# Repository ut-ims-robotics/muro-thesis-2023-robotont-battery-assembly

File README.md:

# muro-thesis-2023-robotont-battery-assembly

## ENG
Welcome to the repository for Robotont's battery assembly mechanics and 12 V voltage regulator. This repository includes KiCad project files, pictures, renders and videos that illustrate development of Robotont.

Production files for battery locking mechanism are part of gen3 Robotont development and can be found at this [repository](https://github.com/robotont/robotont-mechanics).

KiCad project files and production files for battery data adapter can be found at this [repository](https://github.com/robotont/robotont-electronics-battery-adapter).

KiCad project files and production files for voltage regulator can be found at this [folder](https://github.com/ut-ims-robotics/muro-thesis-2023-robotont-battery-assembly/tree/main/12V_DC_DC_converter). The whole design of unified PCB which integrates the voltage regulator can be found at this [repository](https://github.com/robotont/robotont-electronics-mainboard).

## EST 
Tere tulemast Robotondi akumehhanismi ja 12 V pingeregulaatori hoidlasse. Selles hoidlas on KiCadi projektifailid ning leidub samuti pilte, videosid ja 3D visualiseeringuid , mis illustreerivad Robotondi arendusprotsessi.

Aku lukustusmehanismi tootmisfailid on osa gen3 Robotondi arendusest ja asuvad siin [hoidlas](https://github.com/robotont/robotont-mechanics).

KiCadi projekti- ja tootmisfailid aku andmevahetuse adapteri jaoks asuvad siin [hoidlas](https://github.com/robotont/robotont-electronics-battery-adapter).

KiCadi projekti- ja tootmisfailid pingeregulaatori jaoks asuvad siin [kaustas](https://github.com/ut-ims-robotics/muro-thesis-2023-robotont-battery-assembly/tree/main/12V_DC_DC_converter). Kogu ühtse trükkplaadi disain (kuhu on integreeritud ka käesolev pingeregulaator) koos tootmisfailidega asub siin [hoidlas](https://github.com/robotont/robotont-electronics-mainboard).

## Battery Locking Mechanism / Aku Lukustusmehhanism
3D model and prototype of battery locking mechanism for Robotont:

Locking mechanism and battery in 2nd gen robot assembly:

## Battery Data Adapter / Aku Andmevahetuse Adapter
The following figures visualize the front side of the PCB along with the 3D model of the design:

## Voltage Regulator / Pingeregulaator

The following figures visualize the front side of the PCB along with the KiCad model of the design:

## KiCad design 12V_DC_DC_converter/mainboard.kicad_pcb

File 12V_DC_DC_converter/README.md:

# 12 V dc dc converter
Voltage regulator for the 3rd generation robotont robot.

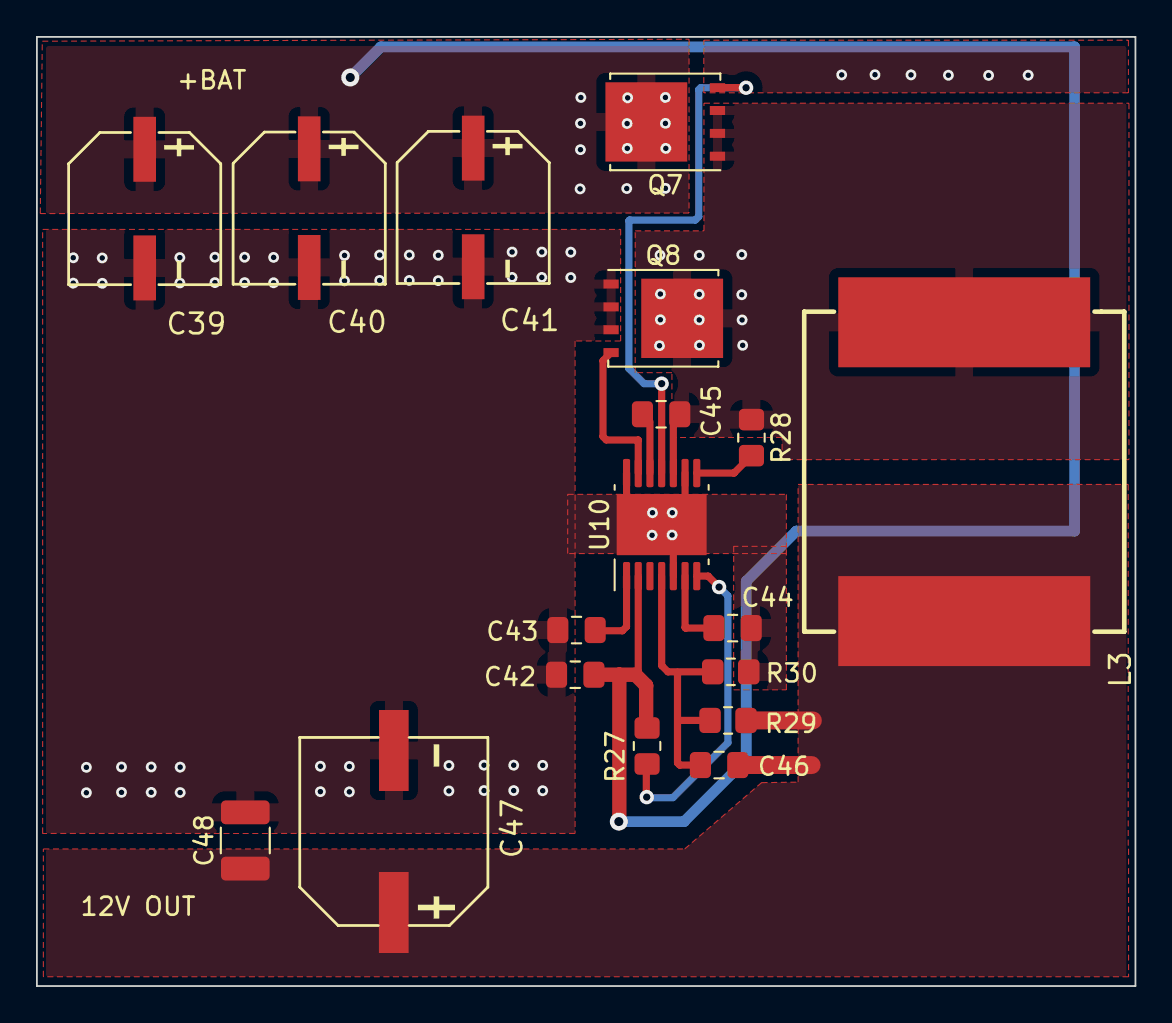
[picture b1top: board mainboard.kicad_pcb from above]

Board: 2 copper layers, 61.0 x 52.7 mm, 18 parts (0 on the bottom side), 12 nets.

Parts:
C39, C40, C41: 39uF; CAP-SMD_BD8.0-L8.3-W8.3-LS9.0-FD_35SVPF39M
C42: 100nF; C_0805_2012Metric_Pad1.18x1.45mm_HandSolder
C43: 2.2uF; C_0805_2012Metric_Pad1.18x1.45mm_HandSolder
C44: 15nF; C_0805_2012Metric_Pad1.18x1.45mm_HandSolder
C45: 470nF; C_0805_2012Metric_Pad1.18x1.45mm_HandSolder
C46: 470pF; C_0805_2012Metric_Pad1.18x1.45mm_HandSolder
C47: 120uF; CAP-SMD_BD10.0-L10.3-W10.3-FD_EEHZC1E331P
C48: 100uF; C_1210_3225Metric_Pad1.33x2.70mm_HandSolder
L3: 4.7uH; IND-SMD_L17.5-W17.5
Q7: CSD17505Q5A; TDSON-8-1
Q8: CSD18540Q5B; TDSON-8-1
R27: 604K; R_0805_2012Metric_Pad1.20x1.40mm_HandSolder
R28: 1.43K; R_0805_2012Metric_Pad1.20x1.40mm_HandSolder
R29: 191K; R_0805_2012Metric_Pad1.20x1.40mm_HandSolder
R30: 10K; R_0805_2012Metric_Pad1.20x1.40mm_HandSolder
U10: LM3150MH; HTSSOP-14-1EP_4.4x5mm_P0.65mm_EP3.4x5mm_Mask3x3.1mm

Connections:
+12V: C46.1, C47.1, C48.1, L3.2, R29.1
+BATT: C39.1, C40.1, C41.1, C42.1, Q7.5 (D), R27.1, U10.2 (VIN)
BST: C45.1, U10.12 (BST)
CVCC: C43.1, U10.1 (VCC)
FB: C46.2, R29.2, R30.1, U10.4 (FB)
GND: C39.2, C40.2, C41.2, C42.2, C43.2, C44.2, C47.2, C48.2, Q8.1 (S), Q8.2 (S), Q8.3 (S), R30.2, U10.5 (SGND), U10.9 (SGND), U10.14 (PGND), U10.15 (SGND)
HG: Q7.4 (G), U10.11 (HG)
ILIM: R28.2, U10.8 (ILIM)
LG: Q8.4 (G), U10.13 (LG)
RON: R27.2, U10.7 (RON)
SS: C44.1, U10.6 (SS)
SW: C45.2, L3.1, Q7.1 (S), Q7.2 (S), Q7.3 (S), Q8.5 (D), R28.1, U10.10 (SW)

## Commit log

2023-05-19 README update
2023-05-19 Added submodule
2023-05-19 updated submodule
2023-05-20 Added 12 V voltage regulator KiCad project files
2023-05-20 Added pictures
2023-05-20 Added renderings
2023-05-20 Added videos
2023-05-20 Added BOM for locking mechanism
